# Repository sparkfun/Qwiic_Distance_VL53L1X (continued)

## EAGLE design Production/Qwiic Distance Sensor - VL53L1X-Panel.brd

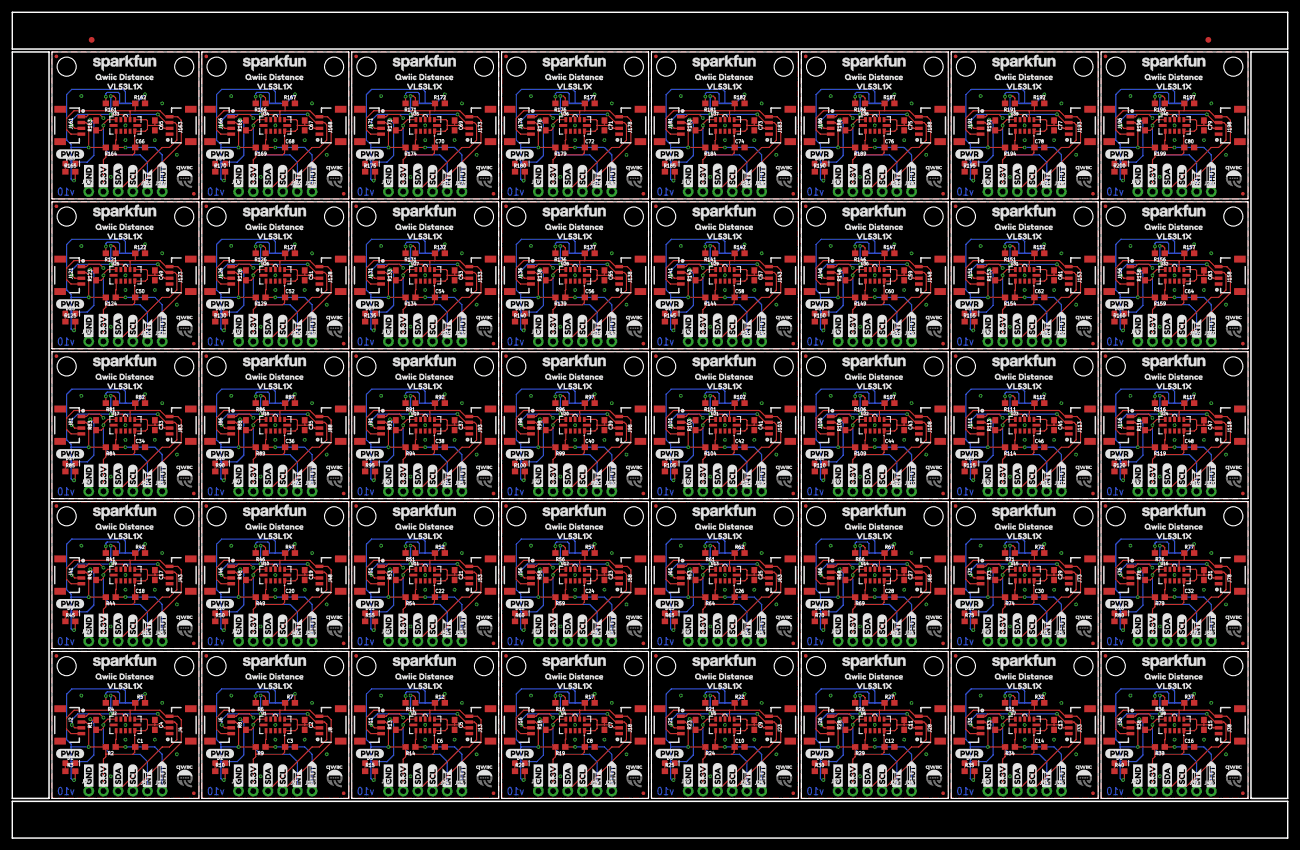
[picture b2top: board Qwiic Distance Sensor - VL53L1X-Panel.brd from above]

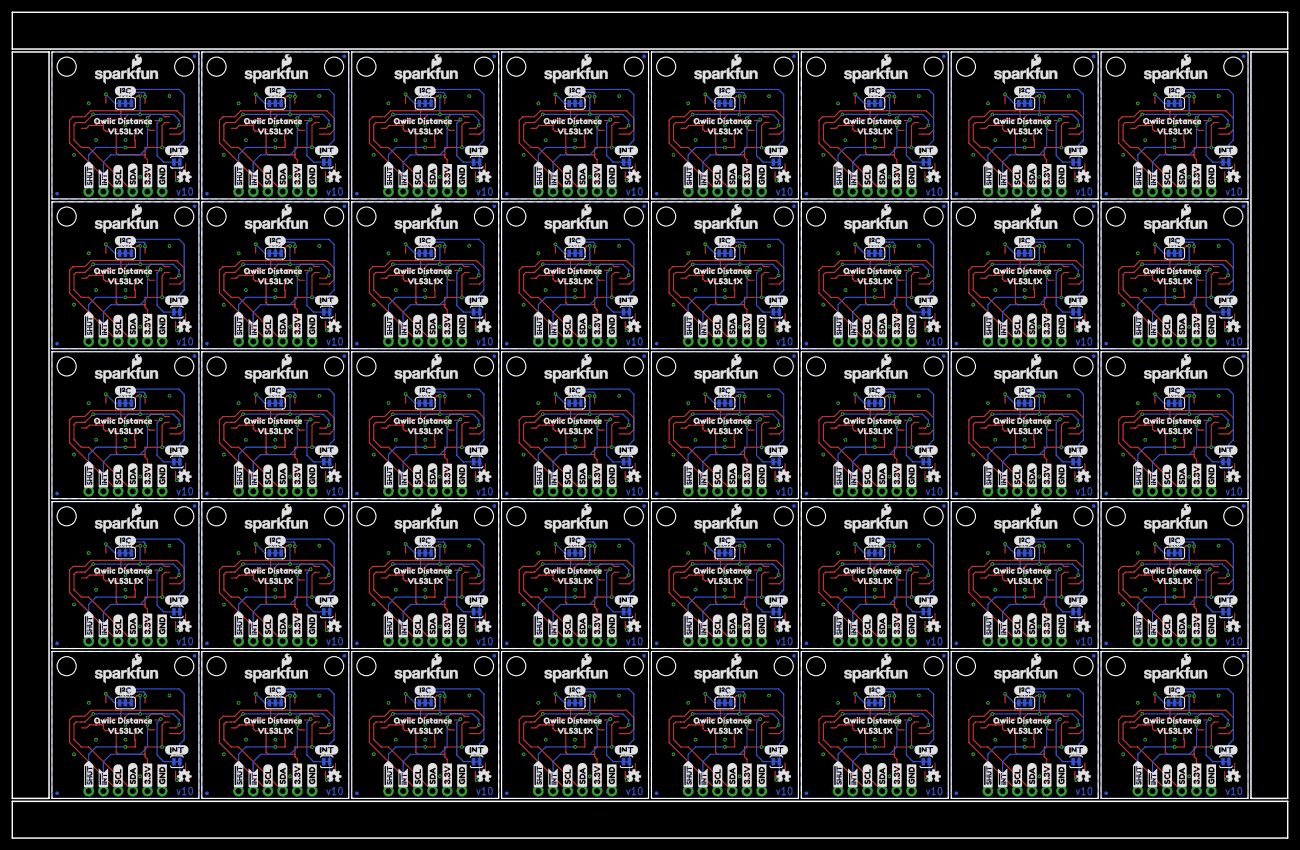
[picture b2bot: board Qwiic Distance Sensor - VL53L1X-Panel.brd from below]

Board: 2 copper layers, 220.5 x 142.7 mm, 1802 parts (640 on the bottom side), 400 nets.

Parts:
C1, C3, C6, C8, C10, C12, C14, C16, C18, C20, C22, C24, C26, C28, C30, C32, C34, C36, C38, C40, C42, C44, C46, C48, C50, C52, C54, C56, C58, C60, C62, C64, C66, C68, C70, C72, C74, C76, C78, C80: 4.7uF; 0603
C2, C4, C5, C7, C9, C11, C13, C15, C17, C19, C21, C23, C25, C27, C29, C31, C33, C35, C37, C39, C41, C43, C45, C47, C49, C51, C53, C55, C57, C59, C61, C63, C65, C67, C69, C71, C73, C75, C77, C79: 0.1uF; 0603
D1, D2, D3, D4, D5, D6, D7, D8, D9, D10, D11, D12, D13, D14, D15, D16, D17, D18, D19, D20, D21, D22, D23, D24, D25, D26, D27, D28, D29, D30, D31, D32, D33, D34, D35, D36, D37, D38, D39, D40: RED; LED-0603
E$1, E$2: FIDUCIAL-1X2
I2C, I2C1, I2C2, I2C3, I2C4, I2C5, I2C6, I2C7, I2C8, I2C9, I2C10, I2C11, I2C12, I2C13, I2C14, I2C15, I2C16, I2C17, I2C18, I2C19, I2C20, I2C21, I2C22, I2C23, I2C24, I2C25, I2C26, I2C27, I2C28, I2C29, I2C30, I2C31, I2C32, I2C33, I2C34, I2C35, I2C36, I2C37, I2C38, I2C39: SMT-JUMPER_3_2-NC_TRACE_SILK
J1, J5, J9, J10, J14, J15, J19, J20, J24, J25, J29, J30, J34, J35, J39, J40, J44, J45, J49, J50, J54, J55, J59, J60, J64, J65, J69, J70, J74, J75, J79, J80, J84, J85, J89, J90, J94, J95, J99, J100, J104, J105, J109, J110, J114, J115, J119, J120, J124, J125, J129, J130, J134, J135, J139, J140, J144, J145, J149, J150, J154, J155, J159, J160, J164, J165, J169, J170, J174, J175, J179, J180, J184, J185, J189, J190, J194, J195, J199, J200: 1X01_NO_SILK
J2, J4, J6, J8, J11, J13, J16, J18, J21, J23, J26, J28, J31, J33, J36, J38, J41, J43, J46, J48, J51, J53, J56, J58, J61, J63, J66, J68, J71, J73, J76, J78, J81, J83, J86, J88, J91, J93, J96, J98, J101, J103, J106, J108, J111, J113, J116, J118, J121, J123, J126, J128, J131, J133, J136, J138, J141, J143, J146, J148, J151, J153, J156, J158, J161, J163, J166, J168, J171, J173, J176, J178, J181, J183, J186, J188, J191, J193, J196, J198: 1X04_1MM_RA
J3, J7, J12, J17, J22, J27, J32, J37, J42, J47, J52, J57, J62, J67, J72, J77, J82, J87, J92, J97, J102, J107, J112, J117, J122, J127, J132, J137, J142, J147, J152, J157, J162, J167, J172, J177, J182, J187, J192, J197: PTH; 1X04_NO_SILK
JP1, JP2, JP5, JP6, JP10, JP11, JP12, JP13, JP17, JP18, JP19, JP20, JP24, JP25, JP26, JP27, JP31, JP32, JP33, JP34, JP38, JP39, JP40, JP41, JP45, JP46, JP47, JP48, JP52, JP53, JP54, JP55, JP59, JP60, JP61, JP62, JP66, JP67, JP68, JP69, JP73, JP74, JP75, JP76, JP80, JP81, JP82, JP83, JP87, JP88, JP89, JP90, JP94, JP95, JP96, JP97, JP101, JP102, JP103, JP104, JP108, JP109, JP110, JP111, JP115, JP116, JP117, JP118, JP122, JP123, JP124, JP125, JP129, JP130, JP131, JP132, JP136, JP137, JP138, JP139, JP143, JP144, JP145, JP146, JP150, JP151, JP152, JP153, JP157, JP158, JP159, JP160, JP164, JP165, JP166, JP167, JP171, JP172, JP173, JP174, JP178, JP179, JP180, JP181, JP185, JP186, JP187, JP188, JP192, JP193, JP194, JP195, JP199, JP200, JP201, JP202, JP206, JP207, JP208, JP209, JP213, JP214, JP215, JP216, JP220, JP221, JP222, JP223, JP227, JP228, JP229, JP230, JP234, JP235, JP236, JP237, JP241, JP242, JP243, JP244, JP248, JP249, JP250, JP251, JP255, JP256, JP257, JP258, JP262, JP263, JP264, JP265, JP269, JP270, JP271, JP272, JP276, JP277, JP278, JP279: FIDUCIALUFIDUCIAL; MICRO-FIDUCIAL
JP3, JP4, JP7, JP8, JP15, JP16, JP22, JP23, JP29, JP30, JP36, JP37, JP43, JP44, JP50, JP51, JP57, JP58, JP64, JP65, JP71, JP72, JP78, JP79, JP85, JP86, JP92, JP93, JP99, JP100, JP106, JP107, JP113, JP114, JP120, JP121, JP127, JP128, JP134, JP135, JP141, JP142, JP148, JP149, JP155, JP156, JP162, JP163, JP169, JP170, JP176, JP177, JP183, JP184, JP190, JP191, JP197, JP198, JP204, JP205, JP211, JP212, JP218, JP219, JP225, JP226, JP232, JP233, JP239, JP240, JP246, JP247, JP253, JP254, JP260, JP261, JP267, JP268, JP274, JP275: STAND-OFF
JP9, JP14, JP21, JP28, JP35, JP42, JP49, JP56, JP63, JP70, JP77, JP84, JP91, JP98, JP105, JP112, JP119, JP126, JP133, JP140, JP147, JP154, JP161, JP168, JP175, JP182, JP189, JP196, JP203, JP210, JP217, JP224, JP231, JP238, JP245, JP252, JP259, JP266, JP273, JP280: INT; PAD-JUMPER-2-NC_BY_TRACE_YES_SILK
LOGO1, LOGO2, LOGO3, LOGO4, LOGO5, LOGO6, LOGO7, LOGO8, LOGO9, LOGO10, LOGO11, LOGO12, LOGO13, LOGO14, LOGO15, LOGO16, LOGO17, LOGO18, LOGO19, LOGO20, LOGO21, LOGO22, LOGO23, LOGO24, LOGO25, LOGO26, LOGO27, LOGO28, LOGO29, LOGO30, LOGO31, LOGO32, LOGO33, LOGO34, LOGO35, LOGO36, LOGO37, LOGO38, LOGO39, LOGO40: OSHW-LOGOMINI; OSHW-LOGO-MINI
R1, R2, R8, R9, R13, R14, R18, R19, R23, R24, R28, R29, R33, R34, R38, R39, R43, R44, R48, R49, R53, R54, R58, R59, R63, R64, R68, R69, R73, R74, R78, R79, R83, R84, R88, R89, R93, R94, R98, R99, R103, R104, R108, R109, R113, R114, R118, R119, R123, R124, R128, R129, R133, R134, R138, R139, R143, R144, R148, R149, R153, R154, R158, R159, R163, R164, R168, R169, R173, R174, R178, R179, R183, R184, R188, R189, R193, R194, R198, R199: 10k; 0603
R3, R10, R15, R20, R25, R30, R35, R40, R45, R50, R55, R60, R65, R70, R75, R80, R85, R90, R95, R100, R105, R110, R115, R120, R125, R130, R135, R140, R145, R150, R155, R160, R165, R170, R175, R180, R185, R190, R195, R200: 1k; 0603
R4, R5, R6, R7, R11, R12, R16, R17, R21, R22, R26, R27, R31, R32, R36, R37, R41, R42, R46, R47, R51, R52, R56, R57, R61, R62, R66, R67, R71, R72, R76, R77, R81, R82, R86, R87, R91, R92, R96, R97, R101, R102, R106, R107, R111, R112, R116, R117, R121, R122, R126, R127, R131, R132, R136, R137, R141, R142, R146, R147, R151, R152, R156, R157, R161, R162, R166, R167, R171, R172, R176, R177, R181, R182, R186, R187, R191, R192, R196, R197: 2.2k; 0603
U1, U2, U3, U4, U5, U6, U7, U8, U9, U10, U11, U12, U13, U14, U15, U16, U17, U18, U19, U20, U21, U22, U23, U24, U25, U26, U27, U28, U29, U30, U31, U32, U33, U34, U35, U36, U37, U38, U39, U40: VL53L1X
U$1, U$18, U$46, U$68, U$90, U$112, U$134, U$156, U$178, U$200, U$222, U$244, U$266, U$288, U$310, U$332, U$354, U$376, U$398, U$420, U$442, U$464, U$486, U$508, U$530, U$552, U$574, U$596, U$618, U$640, U$662, U$684, U$706, U$728, U$750, U$772, U$794, U$816, U$838, U$860: SFE_LOGO_NAME.1_INCH; SFE_LOGO_NAME_.1
U$2, U$17, U$45, U$67, U$89, U$111, U$133, U$155, U$177, U$199, U$221, U$243, U$265, U$287, U$309, U$331, U$353, U$375, U$397, U$419, U$441, U$463, U$485, U$507, U$529, U$551, U$573, U$595, U$617, U$639, U$661, U$683, U$705, U$727, U$749, U$771, U$793, U$815, U$837, U$859: SFE_LOGO_NAME_FLAME.1_INCH; SFE_LOGO_NAME_FLAME_.1
U$3, U$22, U$30, U$33, U$52, U$55, U$74, U$77, U$96, U$99, U$118, U$121, U$140, U$143, U$162, U$165, U$184, U$187, U$206, U$209, U$228, U$231, U$250, U$253, U$272, U$275, U$294, U$297, U$316, U$319, U$338, U$341, U$360, U$363, U$382, U$385, U$404, U$407, U$426, U$429, U$448, U$451, U$470, U$473, U$492, U$495, U$514, U$517, U$536, U$539, U$558, U$561, U$580, U$583, U$602, U$605, U$624, U$627, U$646, U$649, U$668, U$671, U$690, U$693, U$712, U$715, U$734, U$737, U$756, U$759, U$778, U$781, U$800, U$803, U$822, U$825, U$844, U$847, U$866, U$869: GND1
U$4, U$21, U$29, U$34, U$51, U$56, U$73, U$78, U$95, U$100, U$117, U$122, U$139, U$144, U$161, U$166, U$183, U$188, U$205, U$210, U$227, U$232, U$249, U$254, U$271, U$276, U$293, U$298, U$315, U$320, U$337, U$342, U$359, U$364, U$381, U$386, U$403, U$408, U$425, U$430, U$447, U$452, U$469, U$474, U$491, U$496, U$513, U$518, U$535, U$540, U$557, U$562, U$579, U$584, U$601, U$606, U$623, U$628, U$645, U$650, U$667, U$672, U$689, U$694, U$711, U$716, U$733, U$738, U$755, U$760, U$777, U$782, U$799, U$804, U$821, U$826, U$843, U$848, U$865, U$870: 3#3V2
U$5, U$27, U$32, U$35, U$54, U$57, U$76, U$79, U$98, U$101, U$120, U$123, U$142, U$145, U$164, U$167, U$186, U$189, U$208, U$211, U$230, U$233, U$252, U$255, U$274, U$277, U$296, U$299, U$318, U$321, U$340, U$343, U$362, U$365, U$384, U$387, U$406, U$409, U$428, U$431, U$450, U$453, U$472, U$475, U$494, U$497, U$516, U$519, U$538, U$541, U$560, U$563, U$582, U$585, U$604, U$607, U$626, U$629, U$648, U$651, U$670, U$673, U$692, U$695, U$714, U$717, U$736, U$739, U$758, U$761, U$780, U$783, U$802, U$805, U$824, U$827, U$846, U$849, U$868, U$871: SDA8
U$6, U$26, U$31, U$36, U$53, U$58, U$75, U$80, U$97, U$102, U$119, U$124, U$141, U$146, U$163, U$168, U$185, U$190, U$207, U$212, U$229, U$234, U$251, U$256, U$273, U$278, U$295, U$300, U$317, U$322, U$339, U$344, U$361, U$366, U$383, U$388, U$405, U$410, U$427, U$432, U$449, U$454, U$471, U$476, U$493, U$498, U$515, U$520, U$537, U$542, U$559, U$564, U$581, U$586, U$603, U$608, U$625, U$630, U$647, U$652, U$669, U$674, U$691, U$696, U$713, U$718, U$735, U$740, U$757, U$762, U$779, U$784, U$801, U$806, U$823, U$828, U$845, U$850, U$867, U$872: SCL9
U$7, U$14, U$43, U$44, U$65, U$66, U$87, U$88, U$109, U$110, U$131, U$132, U$153, U$154, U$175, U$176, U$197, U$198, U$219, U$220, U$241, U$242, U$263, U$264, U$285, U$286, U$307, U$308, U$329, U$330, U$351, U$352, U$373, U$374, U$395, U$396, U$417, U$418, U$439, U$440, U$461, U$462, U$483, U$484, U$505, U$506, U$527, U$528, U$549, U$550, U$571, U$572, U$593, U$594, U$615, U$616, U$637, U$638, U$659, U$660, U$681, U$682, U$703, U$704, U$725, U$726, U$747, U$748, U$769, U$770, U$791, U$792, U$813, U$814, U$835, U$836, U$857, U$858, U$879, U$880: INT#-[<
U$8, U$9, U$37, U$38, U$59, U$60, U$81, U$82, U$103, U$104, U$125, U$126, U$147, U$148, U$169, U$170, U$191, U$192, U$213, U$214, U$235, U$236, U$257, U$258, U$279, U$280, U$301, U$302, U$323, U$324, U$345, U$346, U$367, U$368, U$389, U$390, U$411, U$412, U$433, U$434, U$455, U$456, U$477, U$478, U$499, U$500, U$521, U$522, U$543, U$544, U$565, U$566, U$587, U$588, U$609, U$610, U$631, U$632, U$653, U$654, U$675, U$676, U$697, U$698, U$719, U$720, U$741, U$742, U$763, U$764, U$785, U$786, U$807, U$808, U$829, U$830, U$851, U$852, U$873, U$874: #SHUT15
U$10, U$39, U$61, U$83, U$105, U$127, U$149, U$171, U$193, U$215, U$237, U$259, U$281, U$303, U$325, U$347, U$369, U$391, U$413, U$435, U$457, U$479, U$501, U$523, U$545, U$567, U$589, U$611, U$633, U$655, U$677, U$699, U$721, U$743, U$765, U$787, U$809, U$831, U$853, U$875: (PWR)
U$11, U$40, U$62, U$84, U$106, U$128, U$150, U$172, U$194, U$216, U$238, U$260, U$282, U$304, U$326, U$348, U$370, U$392, U$414, U$436, U$458, U$480, U$502, U$524, U$546, U$568, U$590, U$612, U$634, U$656, U$678, U$700, U$722, U$744, U$766, U$788, U$810, U$832, U$854, U$876: (I_SUPER2_C)
U$12, U$41, U$63, U$85, U$107, U$129, U$151, U$173, U$195, U$217, U$239, U$261, U$283, U$305, U$327, U$349, U$371, U$393, U$415, U$437, U$459, U$481, U$503, U$525, U$547, U$569, U$591, U$613, U$635, U$657, U$679, U$701, U$723, U$745, U$767, U$789, U$811, U$833, U$855, U$877: (INT)
U$13, U$42, U$64, U$86, U$108, U$130, U$152, U$174, U$196, U$218, U$240, U$262, U$284, U$306, U$328, U$350, U$372, U$394, U$416, U$438, U$460, U$482, U$504, U$526, U$548, U$570, U$592, U$614, U$636, U$658, U$680, U$702, U$724, U$746, U$768, U$790, U$812, U$834, U$856, U$878: QWIIC-LOGO-SMALL
U$15, U$19, U$23, U$25, U$47, U$49, U$69, U$71, U$91, U$93, U$113, U$115, U$135, U$137, U$157, U$159, U$179, U$181, U$201, U$203, U$223, U$225, U$245, U$247, U$267, U$269, U$289, U$291, U$311, U$313, U$333, U$335, U$355, U$357, U$377, U$379, U$399, U$401, U$421, U$423, U$443, U$445, U$465, U$467, U$487, U$489, U$509, U$511, U$531, U$533, U$553, U$555, U$575, U$577, U$597, U$599, U$619, U$621, U$641, U$643, U$663, U$665, U$685, U$687, U$707, U$709, U$729, U$731, U$751, U$753, U$773, U$775, U$795, U$797, U$817, U$819, U$839, U$841, U$861, U$863: QWIIC_DISTANCE0
U$16, U$20, U$24, U$28, U$48, U$50, U$70, U$72, U$92, U$94, U$114, U$116, U$136, U$138, U$158, U$160, U$180, U$182, U$202, U$204, U$224, U$226, U$246, U$248, U$268, U$270, U$290, U$292, U$312, U$314, U$334, U$336, U$356, U$358, U$378, U$380, U$400, U$402, U$422, U$424, U$444, U$446, U$466, U$468, U$488, U$490, U$510, U$512, U$532, U$534, U$554, U$556, U$576, U$578, U$598, U$600, U$620, U$622, U$642, U$644, U$664, U$666, U$686, U$688, U$708, U$710, U$730, U$732, U$752, U$754, U$774, U$776, U$796, U$798, U$818, U$820, U$840, U$842, U$862, U$864: VL53L1X1

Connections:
3.3V: C1.1, C4.1, I2C.2, J2.2, J3.2, J4.2, JP9.2, R2.2, R3.2, U2.1, U2.11
3.3V1: C2.1, C3.1, I2C1.2, J6.2, J7.2, J8.2, JP14.2, R9.2, R10.2, U1.1, U1.11
3.3V2: C5.1, C6.1, I2C2.2, J11.2, J12.2, J13.2, JP21.2, R14.2, R15.2, U3.1, U3.11
3.3V3: C7.1, C8.1, I2C3.2, J16.2, J17.2, J18.2, JP28.2, R19.2, R20.2, U4.1, U4.11
3.3V4: C9.1, C10.1, I2C4.2, J21.2, J22.2, J23.2, JP35.2, R24.2, R25.2, U5.1, U5.11
3.3V5: C11.1, C12.1, I2C5.2, J26.2, J27.2, J28.2, JP42.2, R29.2, R30.2, U6.1, U6.11
3.3V6: C13.1, C14.1, I2C6.2, J31.2, J32.2, J33.2, JP49.2, R34.2, R35.2, U7.1, U7.11
3.3V7: C15.1, C16.1, I2C7.2, J36.2, J37.2, J38.2, JP56.2, R39.2, R40.2, U8.1, U8.11
3.3V8: C17.1, C18.1, I2C8.2, J41.2, J42.2, J43.2, JP63.2, R44.2, R45.2, U9.1, U9.11
3.3V9: C19.1, C20.1, I2C9.2, J46.2, J47.2, J48.2, JP70.2, R49.2, R50.2, U10.1, U10.11
3.3V10: C21.1, C22.1, I2C10.2, J51.2, J52.2, J53.2, JP77.2, R54.2, R55.2, U11.1, U11.11
3.3V11: C23.1, C24.1, I2C11.2, J56.2, J57.2, J58.2, JP84.2, R59.2, R60.2, U12.1, U12.11
3.3V12: C25.1, C26.1, I2C12.2, J61.2, J62.2, J63.2, JP91.2, R64.2, R65.2, U13.1, U13.11
3.3V13: C27.1, C28.1, I2C13.2, J66.2, J67.2, J68.2, JP98.2, R69.2, R70.2, U14.1, U14.11
3.3V14: C29.1, C30.1, I2C14.2, J71.2, J72.2, J73.2, JP105.2, R74.2, R75.2, U15.1, U15.11
3.3V15: C31.1, C32.1, I2C15.2, J76.2, J77.2, J78.2, JP112.2, R79.2, R80.2, U16.1, U16.11
3.3V16: C33.1, C34.1, I2C16.2, J81.2, J82.2, J83.2, JP119.2, R84.2, R85.2, U17.1, U17.11
3.3V17: C35.1, C36.1, I2C17.2, J86.2, J87.2, J88.2, JP126.2, R89.2, R90.2, U18.1, U18.11
3.3V18: C37.1, C38.1, I2C18.2, J91.2, J92.2, J93.2, JP133.2, R94.2, R95.2, U19.1, U19.11
3.3V19: C39.1, C40.1, I2C19.2, J96.2, J97.2, J98.2, JP140.2, R99.2, R100.2, U20.1, U20.11
3.3V20: C41.1, C42.1, I2C20.2, J101.2, J102.2, J103.2, JP147.2, R104.2, R105.2, U21.1, U21.11
3.3V21: C43.1, C44.1, I2C21.2, J106.2, J107.2, J108.2, JP154.2, R109.2, R110.2, U22.1, U22.11
3.3V22: C45.1, C46.1, I2C22.2, J111.2, J112.2, J113.2, JP161.2, R114.2, R115.2, U23.1, U23.11
3.3V23: C47.1, C48.1, I2C23.2, J116.2, J117.2, J118.2, JP168.2, R119.2, R120.2, U24.1, U24.11
3.3V24: C49.1, C50.1, I2C24.2, J121.2, J122.2, J123.2, JP175.2, R124.2, R125.2, U25.1, U25.11
3.3V25: C51.1, C52.1, I2C25.2, J126.2, J127.2, J128.2, JP182.2, R129.2, R130.2, U26.1, U26.11
3.3V26: C53.1, C54.1, I2C26.2, J131.2, J132.2, J133.2, JP189.2, R134.2, R135.2, U27.1, U27.11
3.3V27: C55.1, C56.1, I2C27.2, J136.2, J137.2, J138.2, JP196.2, R139.2, R140.2, U28.1, U28.11
3.3V28: C57.1, C58.1, I2C28.2, J141.2, J142.2, J143.2, JP203.2, R144.2, R145.2, U29.1, U29.11
3.3V29: C59.1, C60.1, I2C29.2, J146.2, J147.2, J148.2, JP210.2, R149.2, R150.2, U30.1, U30.11
3.3V30: C61.1, C62.1, I2C30.2, J151.2, J152.2, J153.2, JP217.2, R154.2, R155.2, U31.1, U31.11
3.3V31: C63.1, C64.1, I2C31.2, J156.2, J157.2, J158.2, JP224.2, R159.2, R160.2, U32.1, U32.11
3.3V32: C65.1, C66.1, I2C32.2, J161.2, J162.2, J163.2, JP231.2, R164.2, R165.2, U33.1, U33.11
3.3V33: C67.1, C68.1, I2C33.2, J166.2, J167.2, J168.2, JP238.2, R169.2, R170.2, U34.1, U34.11
3.3V34: C69.1, C70.1, I2C34.2, J171.2, J172.2, J173.2, JP245.2, R174.2, R175.2, U35.1, U35.11
3.3V35: C71.1, C72.1, I2C35.2, J176.2, J177.2, J178.2, JP252.2, R179.2, R180.2, U36.1, U36.11
3.3V36: C73.1, C74.1, I2C36.2, J181.2, J182.2, J183.2, JP259.2, R184.2, R185.2, U37.1, U37.11
3.3V37: C75.1, C76.1, I2C37.2, J186.2, J187.2, J188.2, JP266.2, R189.2, R190.2, U38.1, U38.11
3.3V38: C77.1, C78.1, I2C38.2, J191.2, J192.2, J193.2, JP273.2, R194.2, R195.2, U39.1, U39.11
3.3V39: C79.1, C80.1, I2C39.2, J196.2, J197.2, J198.2, JP280.2, R199.2, R200.2, U40.1, U40.11
!INT: J5.1, R1.1, U2.7
!INT1: J9.1, R8.1, U1.7
!INT2: J14.1, R13.1, U3.7
!INT3: J19.1, R18.1, U4.7
!INT4: J24.1, R23.1, U5.7
!INT5: J29.1, R28.1, U6.7
!INT6: J34.1, R33.1, U7.7
!INT7: J39.1, R38.1, U8.7
!INT8: J44.1, R43.1, U9.7
!INT9: J49.1, R48.1, U10.7
!INT10: J54.1, R53.1, U11.7
!INT11: J59.1, R58.1, U12.7
!INT12: J64.1, R63.1, U13.7
!INT13: J69.1, R68.1, U14.7
!INT14: J74.1, R73.1, U15.7
!INT15: J79.1, R78.1, U16.7
!INT16: J84.1, R83.1, U17.7
!INT17: J89.1, R88.1, U18.7
!INT18: J94.1, R93.1, U19.7
!INT19: J99.1, R98.1, U20.7
!INT20: J104.1, R103.1, U21.7
!INT21: J109.1, R108.1, U22.7
!INT22: J114.1, R113.1, U23.7
!INT23: J119.1, R118.1, U24.7
!INT24: J124.1, R123.1, U25.7
!INT25: J129.1, R128.1, U26.7
!INT26: J134.1, R133.1, U27.7
!INT27: J139.1, R138.1, U28.7
!INT28: J144.1, R143.1, U29.7
!INT29: J149.1, R148.1, U30.7
!INT30: J154.1, R153.1, U31.7
!INT31: J159.1, R158.1, U32.7
!INT32: J164.1, R163.1, U33.7
!INT33: J169.1, R168.1, U34.7
!INT34: J174.1, R173.1, U35.7
!INT35: J179.1, R178.1, U36.7
!INT36: J184.1, R183.1, U37.7
!INT37: J189.1, R188.1, U38.7
!INT38: J194.1, R193.1, U39.7
!INT39: J199.1, R198.1, U40.7
!SHUT: J1.1, R2.1, U2.5
!SHUT1: J10.1, R9.1, U1.5
!SHUT2: J15.1, R14.1, U3.5
!SHUT3: J20.1, R19.1, U4.5
!SHUT4: J25.1, R24.1, U5.5
!SHUT5: J30.1, R29.1, U6.5
!SHUT6: J35.1, R34.1, U7.5
!SHUT7: J40.1, R39.1, U8.5
!SHUT8: J45.1, R44.1, U9.5
!SHUT9: J50.1, R49.1, U10.5
!SHUT10: J55.1, R54.1, U11.5
!SHUT11: J60.1, R59.1, U12.5
!SHUT12: J65.1, R64.1, U13.5
!SHUT13: J70.1, R69.1, U14.5
!SHUT14: J75.1, R74.1, U15.5
!SHUT15: J80.1, R79.1, U16.5
!SHUT16: J85.1, R84.1, U17.5
!SHUT17: J90.1, R89.1, U18.5
!SHUT18: J95.1, R94.1, U19.5
!SHUT19: J100.1, R99.1, U20.5
!SHUT20: J105.1, R104.1, U21.5
!SHUT21: J110.1, R109.1, U22.5
!SHUT22: J115.1, R114.1, U23.5
!SHUT23: J120.1, R119.1, U24.5
!SHUT24: J125.1, R124.1, U25.5
!SHUT25: J130.1, R129.1, U26.5
!SHUT26: J135.1, R134.1, U27.5
!SHUT27: J140.1, R139.1, U28.5
!SHUT28: J145.1, R144.1, U29.5
!SHUT29: J150.1, R149.1, U30.5
!SHUT30: J155.1, R154.1, U31.5
!SHUT31: J160.1, R159.1, U32.5
!SHUT32: J165.1, R164.1, U33.5
!SHUT33: J170.1, R169.1, U34.5
!SHUT34: J175.1, R174.1, U35.5
!SHUT35: J180.1, R179.1, U36.5
!SHUT36: J185.1, R184.1, U37.5
!SHUT37: J190.1, R189.1, U38.5
!SHUT38: J195.1, R194.1, U39.5
!SHUT39: J200.1, R199.1, U40.5
GND: C1.2, C4.2, D1.C, J2.1, J3.1, J4.1, U2.2, U2.3, U2.4, U2.6, U2.12
GND1: C2.2, C3.2, D2.C, J6.1, J7.1, J8.1, U1.2, U1.3, U1.4, U1.6, U1.12
GND2: C5.2, C6.2, D3.C, J11.1, J12.1, J13.1, U3.2, U3.3, U3.4, U3.6, U3.12
GND3: C7.2, C8.2, D4.C, J16.1, J17.1, J18.1, U4.2, U4.3, U4.4, U4.6, U4.12
GND4: C9.2, C10.2, D5.C, J21.1, J22.1, J23.1, U5.2, U5.3, U5.4, U5.6, U5.12
GND5: C11.2, C12.2, D6.C, J26.1, J27.1, J28.1, U6.2, U6.3, U6.4, U6.6, U6.12
GND6: C13.2, C14.2, D7.C, J31.1, J32.1, J33.1, U7.2, U7.3, U7.4, U7.6, U7.12
GND7: C15.2, C16.2, D8.C, J36.1, J37.1, J38.1, U8.2, U8.3, U8.4, U8.6, U8.12
GND8: C17.2, C18.2, D9.C, J41.1, J42.1, J43.1, U9.2, U9.3, U9.4, U9.6, U9.12
GND9: C19.2, C20.2, D10.C, J46.1, J47.1, J48.1, U10.2, U10.3, U10.4, U10.6, U10.12
GND10: C21.2, C22.2, D11.C, J51.1, J52.1, J53.1, U11.2, U11.3, U11.4, U11.6, U11.12
GND11: C23.2, C24.2, D12.C, J56.1, J57.1, J58.1, U12.2, U12.3, U12.4, U12.6, U12.12
GND12: C25.2, C26.2, D13.C, J61.1, J62.1, J63.1, U13.2, U13.3, U13.4, U13.6, U13.12
GND13: C27.2, C28.2, D14.C, J66.1, J67.1, J68.1, U14.2, U14.3, U14.4, U14.6, U14.12
GND14: C29.2, C30.2, D15.C, J71.1, J72.1, J73.1, U15.2, U15.3, U15.4, U15.6, U15.12
GND15: C31.2, C32.2, D16.C, J76.1, J77.1, J78.1, U16.2, U16.3, U16.4, U16.6, U16.12
GND16: C33.2, C34.2, D17.C, J81.1, J82.1, J83.1, U17.2, U17.3, U17.4, U17.6, U17.12
GND17: C35.2, C36.2, D18.C, J86.1, J87.1, J88.1, U18.2, U18.3, U18.4, U18.6, U18.12
GND18: C37.2, C38.2, D19.C, J91.1, J92.1, J93.1, U19.2, U19.3, U19.4, U19.6, U19.12
GND19: C39.2, C40.2, D20.C, J96.1, J97.1, J98.1, U20.2, U20.3, U20.4, U20.6, U20.12
GND20: C41.2, C42.2, D21.C, J101.1, J102.1, J103.1, U21.2, U21.3, U21.4, U21.6, U21.12
GND21: C43.2, C44.2, D22.C, J106.1, J107.1, J108.1, U22.2, U22.3, U22.4, U22.6, U22.12
GND22: C45.2, C46.2, D23.C, J111.1, J112.1, J113.1, U23.2, U23.3, U23.4, U23.6, U23.12
GND23: C47.2, C48.2, D24.C, J116.1, J117.1, J118.1, U24.2, U24.3, U24.4, U24.6, U24.12
GND24: C49.2, C50.2, D25.C, J121.1, J122.1, J123.1, U25.2, U25.3, U25.4, U25.6, U25.12
GND25: C51.2, C52.2, D26.C, J126.1, J127.1, J128.1, U26.2, U26.3, U26.4, U26.6, U26.12
GND26: C53.2, C54.2, D27.C, J131.1, J132.1, J133.1, U27.2, U27.3, U27.4, U27.6, U27.12
GND27: C55.2, C56.2, D28.C, J136.1, J137.1, J138.1, U28.2, U28.3, U28.4, U28.6, U28.12
GND28: C57.2, C58.2, D29.C, J141.1, J142.1, J143.1, U29.2, U29.3, U29.4, U29.6, U29.12
GND29: C59.2, C60.2, D30.C, J146.1, J147.1, J148.1, U30.2, U30.3, U30.4, U30.6, U30.12
GND30: C61.2, C62.2, D31.C, J151.1, J152.1, J153.1, U31.2, U31.3, U31.4, U31.6, U31.12
GND31: C63.2, C64.2, D32.C, J156.1, J157.1, J158.1, U32.2, U32.3, U32.4, U32.6, U32.12
GND32: C65.2, C66.2, D33.C, J161.1, J162.1, J163.1, U33.2, U33.3, U33.4, U33.6, U33.12
GND33: C67.2, C68.2, D34.C, J166.1, J167.1, J168.1, U34.2, U34.3, U34.4, U34.6, U34.12
GND34: C69.2, C70.2, D35.C, J171.1, J172.1, J173.1, U35.2, U35.3, U35.4, U35.6, U35.12
GND35: C71.2, C72.2, D36.C, J176.1, J177.1, J178.1, U36.2, U36.3, U36.4, U36.6, U36.12
GND36: C73.2, C74.2, D37.C, J181.1, J182.1, J183.1, U37.2, U37.3, U37.4, U37.6, U37.12
GND37: C75.2, C76.2, D38.C, J186.1, J187.1, J188.1, U38.2, U38.3, U38.4, U38.6, U38.12
GND38: C77.2, C78.2, D39.C, J191.1, J192.1, J193.1, U39.2, U39.3, U39.4, U39.6, U39.12
GND39: C79.2, C80.2, D40.C, J196.1, J197.1, J198.1, U40.2, U40.3, U40.4, U40.6, U40.12
unnamed: I2C.1, R5.2
unnamed: I2C.3, R4.2
unnamed: D1.A, R3.1
unnamed: JP9.1, R1.2
unnamed: I2C1.1, R7.2
unnamed: I2C1.3, R6.2
unnamed: JP14.1, R8.2
unnamed: D2.A, R10.1
unnamed: I2C2.1, R12.2
unnamed: I2C2.3, R11.2
unnamed: JP21.1, R13.2
unnamed: D3.A, R15.1
unnamed: I2C3.1, R17.2
unnamed: I2C3.3, R16.2
unnamed: JP28.1, R18.2
unnamed: D4.A, R20.1
unnamed: I2C4.1, R22.2
unnamed: I2C4.3, R21.2
unnamed: JP35.1, R23.2
unnamed: D5.A, R25.1
unnamed: I2C5.1, R27.2
unnamed: I2C5.3, R26.2
unnamed: JP42.1, R28.2
unnamed: D6.A, R30.1
unnamed: I2C6.1, R32.2
unnamed: I2C6.3, R31.2
unnamed: JP49.1, R33.2
unnamed: D7.A, R35.1
unnamed: I2C7.1, R37.2
unnamed: I2C7.3, R36.2
unnamed: JP56.1, R38.2
unnamed: D8.A, R40.1
unnamed: I2C8.1, R42.2
unnamed: I2C8.3, R41.2
unnamed: JP63.1, R43.2
unnamed: D9.A, R45.1
unnamed: I2C9.1, R47.2
unnamed: I2C9.3, R46.2
unnamed: JP70.1, R48.2
unnamed: D10.A, R50.1
unnamed: I2C10.1, R52.2
unnamed: I2C10.3, R51.2
unnamed: JP77.1, R53.2
unnamed: D11.A, R55.1
unnamed: I2C11.1, R57.2
unnamed: I2C11.3, R56.2
unnamed: JP84.1, R58.2
unnamed: D12.A, R60.1
unnamed: I2C12.1, R62.2
unnamed: I2C12.3, R61.2
unnamed: JP91.1, R63.2
unnamed: D13.A, R65.1
unnamed: I2C13.1, R67.2
unnamed: I2C13.3, R66.2
unnamed: JP98.1, R68.2
unnamed: D14.A, R70.1
unnamed: I2C14.1, R72.2
unnamed: I2C14.3, R71.2
unnamed: JP105.1, R73.2
unnamed: D15.A, R75.1
unnamed: I2C15.1, R77.2
unnamed: I2C15.3, R76.2
unnamed: JP112.1, R78.2
unnamed: D16.A, R80.1
unnamed: I2C16.1, R82.2
unnamed: I2C16.3, R81.2
unnamed: JP119.1, R83.2
unnamed: D17.A, R85.1
unnamed: I2C17.1, R87.2
unnamed: I2C17.3, R86.2
unnamed: JP126.1, R88.2
unnamed: D18.A, R90.1
unnamed: I2C18.1, R92.2
unnamed: I2C18.3, R91.2
unnamed: JP133.1, R93.2
unnamed: D19.A, R95.1
unnamed: I2C19.1, R97.2
unnamed: I2C19.3, R96.2
unnamed: JP140.1, R98.2
unnamed: D20.A, R100.1
unnamed: I2C20.1, R102.2
unnamed: I2C20.3, R101.2
unnamed: JP147.1, R103.2
unnamed: D21.A, R105.1
unnamed: I2C21.1, R107.2
unnamed: I2C21.3, R106.2
unnamed: JP154.1, R108.2
unnamed: D22.A, R110.1
unnamed: I2C22.1, R112.2
unnamed: I2C22.3, R111.2
unnamed: JP161.1, R113.2
unnamed: D23.A, R115.1
unnamed: I2C23.1, R117.2
unnamed: I2C23.3, R116.2
unnamed: JP168.1, R118.2
unnamed: D24.A, R120.1
unnamed: I2C24.1, R122.2
unnamed: I2C24.3, R121.2
unnamed: JP175.1, R123.2
unnamed: D25.A, R125.1
unnamed: I2C25.1, R127.2
unnamed: I2C25.3, R126.2
unnamed: JP182.1, R128.2
unnamed: D26.A, R130.1
unnamed: I2C26.1, R132.2
unnamed: I2C26.3, R131.2
unnamed: JP189.1, R133.2
unnamed: D27.A, R135.1
unnamed: I2C27.1, R137.2
unnamed: I2C27.3, R136.2
unnamed: JP196.1, R138.2
unnamed: D28.A, R140.1
unnamed: I2C28.1, R142.2
unnamed: I2C28.3, R141.2
unnamed: JP203.1, R143.2
unnamed: D29.A, R145.1
unnamed: I2C29.1, R147.2
unnamed: I2C29.3, R146.2
unnamed: JP210.1, R148.2
unnamed: D30.A, R150.1
unnamed: I2C30.1, R152.2
unnamed: I2C30.3, R151.2
unnamed: JP217.1, R153.2
unnamed: D31.A, R155.1
unnamed: I2C31.1, R157.2
unnamed: I2C31.3, R156.2
unnamed: JP224.1, R158.2
unnamed: D32.A, R160.1
unnamed: I2C32.1, R162.2
unnamed: I2C32.3, R161.2
unnamed: JP231.1, R163.2
unnamed: D33.A, R165.1
unnamed: I2C33.1, R167.2
unnamed: I2C33.3, R166.2
unnamed: JP238.1, R168.2
unnamed: D34.A, R170.1
unnamed: I2C34.1, R172.2
unnamed: I2C34.3, R171.2
unnamed: JP245.1, R173.2
unnamed: D35.A, R175.1
unnamed: I2C35.1, R177.2
unnamed: I2C35.3, R176.2
unnamed: JP252.1, R178.2
unnamed: D36.A, R180.1
unnamed: I2C36.1, R182.2
unnamed: I2C36.3, R181.2
unnamed: JP259.1, R183.2
unnamed: D37.A, R185.1
unnamed: I2C37.1, R187.2
unnamed: I2C37.3, R186.2
unnamed: JP266.1, R188.2
unnamed: D38.A, R190.1
unnamed: I2C38.1, R192.2
unnamed: I2C38.3, R191.2
unnamed: JP273.1, R193.2
unnamed: D39.A, R195.1
unnamed: I2C39.1, R197.2
unnamed: I2C39.3, R196.2
unnamed: JP280.1, R198.2
unnamed: D40.A, R200.1
SCL: J2.4, J3.4, J4.4, R5.1, U2.10
SCL1: J6.4, J7.4, J8.4, R7.1, U1.10
SCL2: J11.4, J12.4, J13.4, R12.1, U3.10
SCL3: J16.4, J17.4, J18.4, R17.1, U4.10
SCL4: J21.4, J22.4, J23.4, R22.1, U5.10
SCL5: J26.4, J27.4, J28.4, R27.1, U6.10
SCL6: J31.4, J32.4, J33.4, R32.1, U7.10
SCL7: J36.4, J37.4, J38.4, R37.1, U8.10
SCL8: J41.4, J42.4, J43.4, R42.1, U9.10
SCL9: J46.4, J47.4, J48.4, R47.1, U10.10
SCL10: J51.4, J52.4, J53.4, R52.1, U11.10
SCL11: J56.4, J57.4, J58.4, R57.1, U12.10
SCL12: J61.4, J62.4, J63.4, R62.1, U13.10
SCL13: J66.4, J67.4, J68.4, R67.1, U14.10
SCL14: J71.4, J72.4, J73.4, R72.1, U15.10
SCL15: J76.4, J77.4, J78.4, R77.1, U16.10
SCL16: J81.4, J82.4, J83.4, R82.1, U17.10
SCL17: J86.4, J87.4, J88.4, R87.1, U18.10
SCL18: J91.4, J92.4, J93.4, R92.1, U19.10
SCL19: J96.4, J97.4, J98.4, R97.1, U20.10
SCL20: J101.4, J102.4, J103.4, R102.1, U21.10
SCL21: J106.4, J107.4, J108.4, R107.1, U22.10
SCL22: J111.4, J112.4, J113.4, R112.1, U23.10
SCL23: J116.4, J117.4, J118.4, R117.1, U24.10
SCL24: J121.4, J122.4, J123.4, R122.1, U25.10
SCL25: J126.4, J127.4, J128.4, R127.1, U26.10
SCL26: J131.4, J132.4, J133.4, R132.1, U27.10
SCL27: J136.4, J137.4, J138.4, R137.1, U28.10
SCL28: J141.4, J142.4, J143.4, R142.1, U29.10
SCL29: J146.4, J147.4, J148.4, R147.1, U30.10
SCL30: J151.4, J152.4, J153.4, R152.1, U31.10
SCL31: J156.4, J157.4, J158.4, R157.1, U32.10
SCL32: J161.4, J162.4, J163.4, R162.1, U33.10
SCL33: J166.4, J167.4, J168.4, R167.1, U34.10
SCL34: J171.4, J172.4, J173.4, R172.1, U35.10
SCL35: J176.4, J177.4, J178.4, R177.1, U36.10
SCL36: J181.4, J182.4, J183.4, R182.1, U37.10
SCL37: J186.4, J187.4, J188.4, R187.1, U38.10
SCL38: J191.4, J192.4, J193.4, R192.1, U39.10
SCL39: J196.4, J197.4, J198.4, R197.1, U40.10
SDA: J2.3, J3.3, J4.3, R4.1, U2.9
SDA1: J6.3, J7.3, J8.3, R6.1, U1.9
SDA2: J11.3, J12.3, J13.3, R11.1, U3.9
SDA3: J16.3, J17.3, J18.3, R16.1, U4.9
SDA4: J21.3, J22.3, J23.3, R21.1, U5.9
SDA5: J26.3, J27.3, J28.3, R26.1, U6.9
SDA6: J31.3, J32.3, J33.3, R31.1, U7.9
SDA7: J36.3, J37.3, J38.3, R36.1, U8.9
SDA8: J41.3, J42.3, J43.3, R41.1, U9.9
SDA9: J46.3, J47.3, J48.3, R46.1, U10.9
SDA10: J51.3, J52.3, J53.3, R51.1, U11.9
SDA11: J56.3, J57.3, J58.3, R56.1, U12.9
SDA12: J61.3, J62.3, J63.3, R61.1, U13.9
SDA13: J66.3, J67.3, J68.3, R66.1, U14.9
SDA14: J71.3, J72.3, J73.3, R71.1, U15.9
SDA15: J76.3, J77.3, J78.3, R76.1, U16.9
SDA16: J81.3, J82.3, J83.3, R81.1, U17.9
SDA17: J86.3, J87.3, J88.3, R86.1, U18.9
SDA18: J91.3, J92.3, J93.3, R91.1, U19.9
SDA19: J96.3, J97.3, J98.3, R96.1, U20.9
SDA20: J101.3, J102.3, J103.3, R101.1, U21.9
SDA21: J106.3, J107.3, J108.3, R106.1, U22.9
SDA22: J111.3, J112.3, J113.3, R111.1, U23.9
SDA23: J116.3, J117.3, J118.3, R116.1, U24.9
SDA24: J121.3, J122.3, J123.3, R121.1, U25.9
SDA25: J126.3, J127.3, J128.3, R126.1, U26.9
SDA26: J131.3, J132.3, J133.3, R131.1, U27.9
SDA27: J136.3, J137.3, J138.3, R136.1, U28.9
SDA28: J141.3, J142.3, J143.3, R141.1, U29.9
SDA29: J146.3, J147.3, J148.3, R146.1, U30.9
SDA30: J151.3, J152.3, J153.3, R151.1, U31.9
SDA31: J156.3, J157.3, J158.3, R156.1, U32.9
SDA32: J161.3, J162.3, J163.3, R161.1, U33.9
SDA33: J166.3, J167.3, J168.3, R166.1, U34.9
SDA34: J171.3, J172.3, J173.3, R171.1, U35.9
SDA35: J176.3, J177.3, J178.3, R176.1, U36.9
SDA36: J181.3, J182.3, J183.3, R181.1, U37.9
SDA37: J186.3, J187.3, J188.3, R186.1, U38.9
SDA38: J191.3, J192.3, J193.3, R191.1, U39.9
SDA39: J196.3, J197.3, J198.3, R196.1, U40.9

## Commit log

2018-05-03 Moving to Reds
2018-05-03 updated silk
2018-05-03 updating Qwiic connectors
2018-05-14 changing INT silk
2018-05-14 post review changes
2018-05-21 Fixing issues
2018-05-29 created panel v10
2018-06-14 updating hardware with gitignore
2018-06-14 adding gitignore
2018-07-17 changed distance between boards for v-scoring
2020-06-24 x01 ordered
    Exact clone of VL53L1X Board with different silk
2020-06-29 Revert "x01 ordered"
    This reverts commit 0e4841487b21f37b9834273fb5b77fccae1b5381.
